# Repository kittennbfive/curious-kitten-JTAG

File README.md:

# curious-kitten-JTAG
  
*Hey kitten, find the JTAG-interface!*  

## What is this?
This is my version of the well-known [JTAGulator](http://www.grandideastudio.com/jtagulator/), made from scratch using different components and my own code. It is work in progress. I appreciate constructive feedback and testing, especially because i don't have a lot of targets to try my tool on.

## Licence and disclaimer
All code is licenced under AGPLv3+. The hardware (schematics, PCB-layout) is distributed under CC BY-SA 4.0. Everything is provided WITHOUT ANY WARRANTY! It is experimental stuff! Before using this tool for reverse-engineering please make sure it is legal to do so in your country. Also note that messing with unknown pins on a device can have nasty consequences, from crashes to fried silicon or even fatal explosions. As i said, **use at your own risk!**

## You need a JTAGulator? It's for sale, just buy one!
Well, the JTAGulator is certainly a really nice tool, but it is quite expensive (Parallax sells them for $189.00 as of today; Adafruit for $199.95). I wanted to make a more economic and simpler version and add some extra-features (with more or less success, read on...).

## Overview and features
The main part of this tool is an ATmega16A. It's available in DIP, has quite a few GPIOs and i had some in my parts bin. As many, many IC it is (sadly) currently unobtainium from the well-known distributors, but you can still get it on Aliexpress. The older ATmega16 without A should work fine too. Other main parts are 2 CD4067 (modules from Aliexpress) and 2 74HC595 (Aliexpress too).  

### Features/Specifications
* 24 channels
* can work with 3,3V or 5V as does your DUT (device under test) or - **NEW** - with optional levelshifters down to 1,2V (TXS0108E) (some commands/features will be unavailable in this mode)
* generic serial interface (115200 8N1), no special software or drivers needed on your PC
* automatic detection of IO-type (input or output, floating or with a pullup/down) to avoid driving outputs and to speed up the brute-force JTAG searching. This feature does not really work as intended for reasons i can't change. See below. *not available when using levelshifters*
* possibility to do some basic exploration of a found JTAG-interface (number of TAP in the chain, ...) (*)
* possibility to "wiggle" several other pins while searching for JTAG in case there is some "Reset", "JTAG-enable" or other signal that need to be driven high/low to make JTAG work. *not yet supported in levelshifter mode*
* pluggable current limiting resistors (THT parts or small extra PCB with SMD) for flexibility
* easy to make so mainly DIP, i only used SMD for a few passives because it's convenient (and 0805 is still quite easy to solder). You could redesign the entire board without any SMD-part. Using a few SMD-parts i managed to get the 2 layer PCB just under 10x10cm (-> cheap to manufacture).
* (much) cheaper than the JTAGulator. I did not do the maths but i would guess $30 or less as a ballpark figure.
* (planed) possibility to reset the DUT while searching for JTAG or doing other stuff (polarity of reset-signal configurable)
* (planed) possibility to power-cycle the DUT (MOSFET)
* (planed) monitoring of the current consumption of the DUT / overcurrent-protection
  
The planed features are currently not implemented but might be at some point. The PCB has spots for most of the needed components, except for the current-monitoring for which there are only testpads to connect an extra PCB. I did it this way because i was in a hurry to order the PCB and didn't had time to select an appropriate high-side current-sense IC (that would probably be unobtainium anyway...). Also selecting an "appropriate" IC to be put onto the main PCB directly is difficult (or even impossible) because there can be many different DUT, from portable stuff using microamps to big stuff using amps (or even AC or something).  

(*) Notice: This tool is not meant to be an universal JTAG-adapter, but rather a search tool. Once you identified the pins i suggest using a dedicated JTAG-adapter (i have a FT232H - beware it's 3,3V - that works great for this and other purposes) and some software like OpenOCD to read the IDENT-register (if it exists) and further mess with your DUT.

## Theory of operation
Having a copy of the schematic (`schematic.pdf`) and the code at hand while reading this part is recommanded.

### Overview/Basics
The ATmega16A is obviously the brain of the entire device. It receives commands via UART and uses a custom parser to dispatch to whatever function is wanted by the user. Each of the 24 channels is connected (via a current limiting resistor for safety) to a GPIO of the AVR. This allows the channel/pin to be an input (high-Z or with pullup) or an output. The two CD4067 are used to route the selected channel to an analog input of the internal ADC. They also allow to put a high-impedance signal (Vcc/2) on a channel for floating input detection. Because i needed a few more pins mainly to control the 4067 i added two 74HC595 with software-SPI on the AVR.
  
### IO-type identification
As said above the AVR will try to autodetect what is connected to each channel, ie
* an active (->low output impedance) digital output (or a direct connection to Vcc or GND, this is impossible to tell, just power everything off and use a multimeter in continuity mode to find Vcc/GND-pins and don't connect them to the AVR - although doing so should be safe because of the current limiting resistors)
* a floating input
* an input with a pullup to Vcc
* an input with a pulldown to GND
* some analog stuff or some variable signal that doesn't look digital (these pins will be ignored later).
#### Algorithm
The code i describe here is located in `pindir_ident.c`. It uses the following approach:
1. connect a high-impedance signal of Vcc/2 (voltage divider using 2 470k resistors) to the tested channel and measure the voltage using the internal ADC several times. If the values are fluctuating a lot the channel is probably not a digital IO -> ignore it. If the voltage is stable at around Vcc/2 we probably have a floating input. As you can see in the schematic both CD4067 have the Vcc/2-signal on a pin, so enabling *both* with the correct settings will connect Vcc/2 to the channel and also the channel to the analog input of the AVR.
2. configure the AVR-GPIO corresponding to the channel as an output, switch it to GND and then Vcc and measure the voltage once for each level. Because we could have an output of the DUT connected to the channel we need the protection resistors here to avoid blowing stuff up. If the measured voltage remains near Vcc or GND in both states we have either an active output (->low impedance) or a direct connection to Vcc/GND.
3. If the voltage drops to (almost) 0V with the AVR outputting a low-signal the channel is probably connected to an input with a pullup.
4. If the voltage goes up to (almost) Vcc while the AVR outputs a high-signal the channel is probably connected to an input with a pulldown.
#### Limitations
Obviously this approach is not perfect, for several reasons:
- Depending on the value used for the protection resistor the AVR might not be able to override a pullup/down completly, the voltage will be *somewhere between* Vcc and GND and the identification of the channel will fail. However using a too small protection resistor value could damage the DUT and/or the AVR.
- The value of pullups/pulldowns is variable between devices, it can be as low as let's say 1k or as high as let's say 470k. This makes automatic detection tricky.
- The state of a pin on the DUT can change, ie an output can be in high-Z mode when the AVR scans the channels. This is especially true for TDO on some (a lot? all?) devices if the JTAG state-machine is in reset or idle-mode where it usually will be. Optionally on some devices the TDO-pin has a pullup too.
- An output can toogle while the AVR scans the channels, in this case the AVR could report an analog pin to be ignored because the voltage changed a lot between measurements (step 1 above). *In doubt check with a scope.*  
  
All values used for this algorithm are configurable at compile-time (#define) and some tweaking might be needed. Sadly i don't have a lot of different devices with JTAG to test my code. I don't think there is enough space left in the AVR to make all these values *runtime*-configurable.

### Searching for JTAG
The code is in file `jtag.c`. I assume you are familiar with JTAG, if not please ask Wikipedia or a local expert or ...
#### The basic idea
Well, i did not invent anything. There are several documented tools like mine on the internet and some really useful papers and presentations available. The basic idea is always to try all possible combinations of pins/channels while sending some valid instructions/data. Precisely my tool tries to set all TAP (there might be several chained!) in BYPASS-mode (luckely this command is standardised), then clock in some known pattern on TDI and watch if it comes back on TDO.
#### Optimisations
To make things faster my code will monitor all possible outputs of the DUT *at the same time*. This can dramatically speed up things. Also the specification for JTAG recommands (or is it even mandatory?) pullups on TDI and TMS, so there is an option in the code to only consider inputs of the DUT that have these pullups as candidates for TDI and TMS.
#### Searching with pin-wiggling enabled
*not (yet) supported in levelshifter mode*  
As i said there might be (are they actually?) some DUT that needs some inputs to be pulled high/low to enable JTAG (i would appreciate an example of a device if you know one). The current code allows you to specify the number of pins to be wiggled simultaneously (because trying all combinations on like 20 pins would take *ages* and is probably rarely if ever needed). It will then try all possible combinations on the number of specified channels while looking for JTAG on the remaining channels. To speed things up the AVR will not set pins that already have a pullup/down to high/low but skip the concerned combinations.

## Exploring the (hopefully) discovered interface
Again, i did not invent anything.
### Get number of TAP in the chain
This works because the BYPASS-instruction is mandatory and standardised and the corresponding data register is always 1 bit wide. The code will set all TAP to BYPASS, clock in a lot of '1' to all the data registers and then clock in a single '0' and count how many clock cycles it takes for this '0' to get trough the chain. 
### Get the length of the instruction register
The basic idea is the same as above. Clock in a lot of '1' to the IR, then clock in a single '0' and wait for it to come back on TDO.
### Get the lengths of the data registers
Same as above except that that *data register* is probed and this for every single possible instruction. **Dangerous, see below!**

## The serial interface / commands
The serial interface runs at 115200 8N1 with the same voltage as the AVR (3,3V or 5V - be careful to select an appropriate USB-to-UART-thingie). Each command is terminated with enter. Currently backspace does not work (might be fixed at some point) and there is no way to scroll to already tipped commands like inside a Linux-terminal (won't be implemented). By default the AVR will send back/mirror entered characters, this can be configured at compile-time (inside `main.c`).
### reset
Well, this should be clear. Reset everything, configure all channels as inputs, ...
### allinp
Configure all channels as inputs without pullup but don't forget anything else that has been configured/discovered.
### devmode (normal|shift)
Switch between "normal" mode (full functionality but limited to 3,3V-5V) and levelshifter ("shift") mode. See below.
### channels $nb
Set the number of used channels, from 4 to 24. Don't make this number bigger than needed because the more channels are used the slower is the search for JTAG. This command is usually the first you need to use (in normal mode).
### ident (*not available in levelshifter mode*)
Do automated IO-type identification and print summary. This command is usually the second command you want to use.  
The following characters/abbreviations are used. The directions are seen from the view of the DUT.
- `--` Channel was not probed.
- `??` Identification failed.
- `a ` Channel might be an analog voltage or something that was fluctuating during the probing.
- `d ` Channel was disabled by user.
- `I ` Floating input.
- `PU` Input with pullup resistor.
- `PD` Input with pulldown resistor.
- `O ` Output.
### chstate
Print summary of set IO-types, useful if you get lost after manual adjustments (see below).
### setmode $channel $mode (*not available in levelshifter mode*)
Manually set the mode of a channel. Be aware that if you use `ident` again your changes will be lost.  
$channel is a number from 0 to 23.  
$mode can be one of "disabled", "input", "inputPU" (input with pullup), "inputPD" (input with pulldown), "output". The directions are seen from the DUT, ie "output" means the channel is an output on the DUT.
### override (inputs|unknown) (yes|no) (*not available in levelshifter mode*)
As i said above the automated IO-type detection is far from perfect. A (currently inactive) output of the DUT will be detected as input, so sometimes you won't see any outputs on the summary (command `chstate`). However JTAG always has one output, so there must be at least one channel configured as an output on the DUT to make the JTAG-search work. The command `override inputs yes` tells the code to also check channels that where detected as DUT-inputs for valid data (TDO). The command `override unknown yes` tells the code to also consider (ie *not* ignore) channels for which the IO-type couldn't been autodetected. *This is potentially dangerous for your DUT!* Remember the disclaimer above.
### tdopullup (yes|no) (*not available in levelshifter mode*)
Enable the internal pullup of the AVR before checking a channel for valid TDO-data. This is needed to detect the JTAG-interface of a "naked" ATmega16A. I don't really understand this as the datasheet states that TDO is left floating but only while the state machine is not shifting data (bug in my code??). You probably don't need this but it might be worth a try if everything else fails. Note that the protection resistor must not be a too high value because this will prevent the DUT from pulling the input of the AVR low! With something like 1k it's fine, with like 47k it is not. 
### jtag1 [ignore] [dontstop]
This is the actual search-command *without* pin-wiggling. It can take up to 2 optional arguments:
- `ignore` tells the code to not consider channels/pins that don't have the mandatory(?) pullup as possible candidates for TDI and TMS. Using this option can dramatically speed up the search but it might fail if there is no pullup on TDI and/or TMS or if the autodetection (`ident`) didn't work. *not available in levelshifter mode*
- `dontstop` tells the code *not* to stop after having found a valid JTAG interface. This is useful as a sanity check, normally there should be a single JTAG-interface. If the code reports a lot of them there is something wrong, in case of a naked ATmega16A it is the pullup on TDO that is missing (use `tdopullup yes`).
### jtag2 $number_of_pins_to_wiggle [ignore]
(*not yet available in levelshifter mode*)  
This is the command for searching while "wiggling" the specified number of pins (try `jtag1` first and then `jtag2 1`). Optionally you can specify `ignore` as for `jtag1`, see just above.
### setlevel $channel (0/1)
Set a channel that is configured / was detected as an output to low or high. This can be used for setting needed pins found by `jtag2`.
### taps
Get the number of TAP in the chain. Will only work if a JTAG-interface has been detected by the search-functions. If it reports 0 something is wrong, check everything and maybe try `jtag1 dontstop`, see above.
### irlen
Get the length of the instruction register. Will only work if `taps` detected a single tap.
### drlen
Get the lengths of the data registers for each instruction. Will only work if `taps` detected a single tap and `drlen` detected a valid length (!=0). **WARNING: This can REALLY mess up your DUT as it writes to every data register without knowing the effects! Use with great caution and - i say it again - at your own risk!**

## Optional levelshifter-support
To be able to probe some DUT that uses 1,8V i made this uh - contraption with 3 TXS0108E modules. It's somewhat messy but i didn't want to wait for an industrial PCB.
  
In this mode power the main board from 5V and type `devmode shift` as first command.  
A conceptual schematic of this module is in `levelshifter.pdf`. Adjust this depending on the hardware you have (IC or modules or other levelshifters). I don't have a PCB-layout or similar stuff.  
The TXS0108E is unobtainium from the well-known distributors (back in stock estimated in 2024! :( ), but you can get modules from places like Aliexpress. However 2 out of 3 modules i ordered have one broken channel ([insert nasty words here]), so i added some code to ignore defective channels (configurable at compile-time) while waiting for replacement IC. Look at `channels.c`.

## Statistics
```
$ cloc *.c *.h
      17 text files.
      17 unique files.                              
       0 files ignored.

github.com/AlDanial/cloc v 1.86  T=0.02 s (1106.0 files/s, 129537.0 lines/s)
-------------------------------------------------------------------------------
Language                     files          blank        comment           code
-------------------------------------------------------------------------------
C                                9            318             85           1325
C/C++ Header                     8             76             45            142
-------------------------------------------------------------------------------
SUM:                            17            394            130           1467
-------------------------------------------------------------------------------
```
The ATmega16A is already quite full, not too much space left... Compiled with -O2 as we want speed but with -O3 the firmware does not fit into the available 16kB.
```
$ avr-size avr.elf
   text	   data	    bss	    dec	    hex	filename
  13988	    432	    154	  14574	   38ee	avr.elf
```

## Example output
The file `log_jtag_atmega16a.txt` contains a complete example/log while searching for the (documented but let's suppose it isn't) JTAG-interface of an ATmega16A.  
The file `log_jtag_fpga.txt` contains the same thing for some FPGA-board.

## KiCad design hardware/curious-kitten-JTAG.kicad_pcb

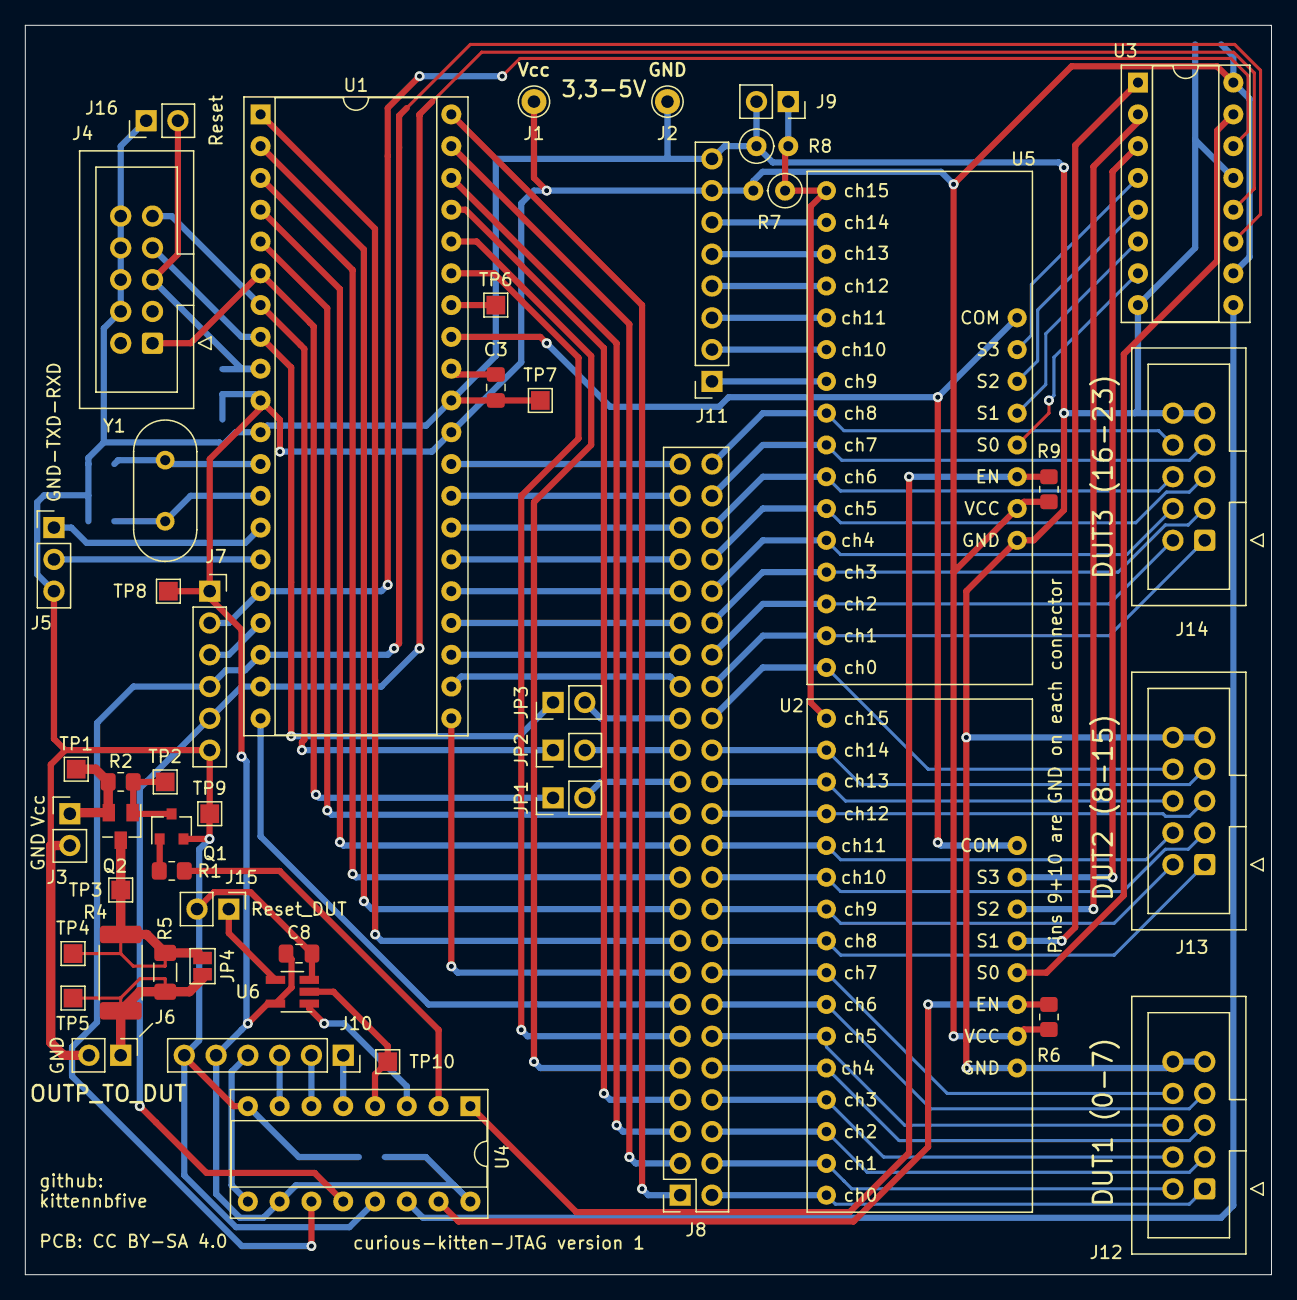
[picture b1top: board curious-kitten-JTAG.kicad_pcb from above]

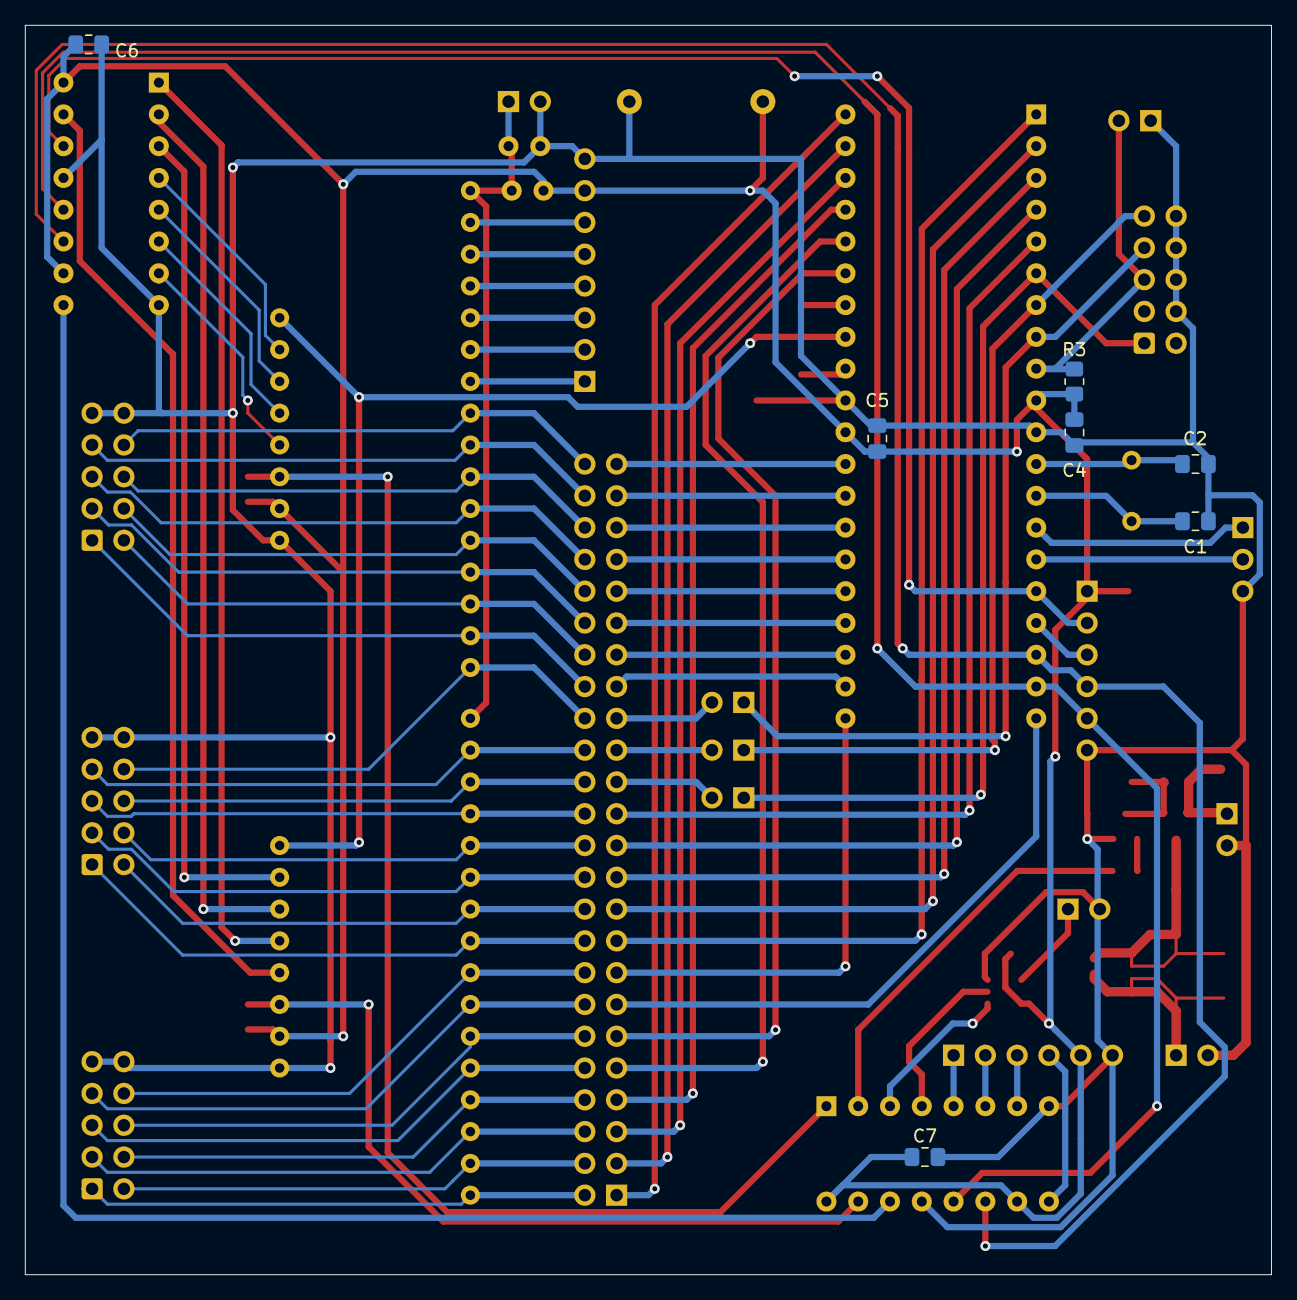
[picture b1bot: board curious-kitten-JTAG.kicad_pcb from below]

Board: 2 copper layers, 99.6 x 99.8 mm, 56 parts (7 on the bottom side), 96 nets.

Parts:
C1, C2: 22p; C_0805_2012Metric_Pad1.18x1.45mm_HandSolder
C3, C4, C5, C6, C7, C8: 100n; C_0805_2012Metric_Pad1.18x1.45mm_HandSolder
J1: Vcc; Pin_D1.0mm_L10.0mm
J2: GND; Pin_D1.0mm_L10.0mm
J3: Vcc_DUT_in; PinHeader_1x02_P2.54mm_Vertical
J4: prog; IDC-Header_2x05_P2.54mm_Vertical
J5: UART; PinHeader_1x03_P2.54mm_Vertical
J6: Vcc_DUT_out; PinHeader_1x02_P2.54mm_Vertical
J7: ext_SPI; PinSocket_1x06_P2.54mm_Vertical
J8: resistors; PinSocket_2x24_P2.54mm_Vertical
J9: half_Vcc; PinSocket_1x02_P2.54mm_Vertical
J10: ext_595_2; PinSocket_1x06_P2.54mm_Vertical
J11: ext_4067; PinSocket_1x08_P2.54mm_Vertical
J12: DUT_1; IDC-Header_2x05_P2.54mm_Vertical
J13: DUT_2; IDC-Header_2x05_P2.54mm_Vertical
J14: DUT_3; IDC-Header_2x05_P2.54mm_Vertical
J15: Reset_DUT_out; PinHeader_1x02_P2.54mm_Vertical
J16: Reset_AVR; PinHeader_1x02_P2.54mm_Vertical
JP1, JP2, JP3: Jumper_2_Bridged; PinHeader_1x02_P2.54mm_Vertical
JP4: SolderJumper_2_Open; SolderJumper-2_P1.3mm_Open_Pad1.0x1.5mm
Q1: BC847; SOT-23
Q2: FDN306P; SuperSOT-3
R1: 1k; R_0805_2012Metric_Pad1.20x1.40mm_HandSolder
R2, R3: 10k; R_0805_2012Metric_Pad1.20x1.40mm_HandSolder
R4: shunt1; R_2512_6332Metric_Pad1.40x3.35mm_HandSolder
R5: shunt2; R_1206_3216Metric_Pad1.30x1.75mm_HandSolder
R6, R9: 100k; R_0805_2012Metric_Pad1.20x1.40mm_HandSolder
R7, R8: 100k; R_Axial_DIN0207_L6.3mm_D2.5mm_P2.54mm_Vertical
TP1, TP2, TP3, TP4, TP5, TP6, TP7, TP8, TP9, TP10: TestPoint; TestPoint_Pad_1.5x1.5mm
U1: ATmega16A-PU; DIP-40_W15.24mm_Socket
U2, U5: CD4067_module
U3, U4: 74HC595; DIP-16_W7.62mm_Socket
U6: SN74LVC1G125DBVR; SOT-23-5_HandSoldering
Y1: 7,3728M; Crystal_HC49-U_Vertical

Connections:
/4067_1_A: U2.10, U3.15
/4067_1_B: U2.11, U3.1
/4067_1_C: U2.14, U3.2
/4067_1_D: U2.13, U3.3
/4067_1_EN: R6.1, U2.15, U4.15
/4067_2_A: U3.7, U5.10
/4067_2_B: U3.6, U5.11
/4067_2_C: U3.5, U5.14
/4067_2_D: U3.4, U5.13
/4067_2_EN: R9.1, U4.1, U5.15
/CLK: J7.4, U1.18, U3.11, U4.11
/MOSI: J7.2, U1.16, U3.14
/RST_DUT_en: U4.3, U6.1
/RST_DUT_sig: TP10.1, U4.4, U6.2
/RXD: J5.1, U1.14
/Reset: J4.5, J16.2, R3.1, U1.9
/TXD: J5.2, U1.15
/avr_ch0: J8.1, U1.40
/avr_ch1: J8.3, U1.39
/avr_ch2: J8.5, U1.38
/avr_ch3: J8.7, U1.37
/avr_ch4: J8.9, U1.36
/avr_ch5: J8.11, U1.35
/avr_ch6: J8.13, U1.20
/avr_ch7: J8.15, U1.21
/avr_ch8: J8.17, U1.1
/avr_ch9: J8.19, U1.2
/avr_ch10: J8.21, U1.3
/avr_ch11: J8.23, U1.4
/avr_ch12: J8.25, U1.5
/avr_ch13: J8.27, JP1.2
/avr_ch14: J8.29, JP2.2
/avr_ch15: J8.31, JP3.2
/avr_ch16: J8.33, U1.22
/avr_ch17: J8.35, U1.23
/avr_ch18: J8.37, U1.24
/avr_ch19: J8.39, U1.25
/avr_ch20: J8.41, U1.26
/avr_ch21: J8.43, U1.27
/avr_ch22: J8.45, U1.28
/avr_ch23: J8.47, U1.29
/ch0: J8.2, J12.1, U2.9
/ch1: J8.4, J12.2, U2.8
/ch2: J8.6, J12.3, U2.7
/ch3: J8.8, J12.4, U2.6
/ch4: J8.10, J12.5, U2.5
/ch5: J8.12, J12.6, U2.4
/ch6: J8.14, J12.7, U2.3
/ch7: J8.16, J12.8, U2.2
/ch8: J8.18, J13.1, U2.23
/ch9: J8.20, J13.2, U2.22
/ch10: J8.22, J13.3, U2.21
/ch11: J8.24, J13.4, U2.20
/ch12: J8.26, J13.5, U2.19
/ch13: J8.28, J13.6, U2.18
/ch14: J8.30, J13.7, U2.17
/ch15: J8.32, J13.8, U5.9
/ch16: J8.34, J14.1, U5.8
/ch17: J8.36, J14.2, U5.7
/ch18: J8.38, J14.3, U5.6
/ch19: J8.40, J14.4, U5.5
/ch20: J8.42, J14.5, U5.4
/ch21: J8.44, J14.6, U5.3
/ch22: J8.46, J14.7, U5.2
/ch23: J8.48, J14.8, U5.23
/half_Vcc: J9.1, R7.1, R8.2, U2.16, U5.16
/latch_595: J7.5, U1.19, U3.12, U4.12
/prog_MISO: J4.9, JP2.1, U1.7
/prog_MOSI: J4.1, JP1.1, U1.6
/prog_SCK: J4.7, JP3.1, U1.8
/sense_curr_DUT: TP6.1, U1.34
/sense_pin: U1.33, U2.1, U5.1
/switch_Vcc_DUT: R1.2, U4.2
GND: C1.2, C2.1, C3.1, C4.2, C5.2, C6.2, C7.2, C8.2, J2.1, J3.2, J4.4, J4.6, J4.8, J4.10, J5.3, J6.2, J7.6, J9.2, J10.6, J11.8, J12.9, J12.10, J13.9, J13.10, J14.9, J14.10, J15.2, J16.1, Q1.2, R8.1, TP7.1, TP9.1, U1.11, U1.31, U2.12, U3.8, U3.13, U4.8, U4.13, U5.12, U6.3
unnamed: C1.1, U1.13, Y1.1
unnamed: C2.2, U1.12, Y1.2
unnamed: C3.2, U1.32
unnamed: J3.1, Q2.2, R2.1, TP1.1
unnamed: J6.1, JP4.2, R4.1, R5.1, TP5.1
unnamed: J7.3, U1.17
unnamed: J10.1, U4.5
unnamed: J10.2, U4.6
unnamed: J10.3, U4.7
unnamed: J10.4, U4.9
unnamed: J11.1, U5.22
unnamed: J11.2, U5.21
unnamed: J11.3, U5.20
unnamed: J11.4, U5.19
unnamed: J11.5, U5.18
unnamed: J11.6, U5.17
unnamed: J15.1, U6.4
unnamed: JP4.1, Q2.3, R4.2, R5.2, TP3.1, TP4.1
unnamed: Q1.1, R1.1
unnamed: Q1.3, Q2.1, R2.2, TP2.1
unnamed: U3.9, U4.14
VCC: C4.1, C5.1, C6.1, C7.1, C8.1, J1.1, J7.1, J10.5, J11.7, R3.2, R6.2, R7.2, R9.2, TP8.1, U1.10, U1.30, U2.24, U3.10, U3.16, U4.10, U4.16, U5.24, U6.5

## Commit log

2022-09-02 typo

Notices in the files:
hardware/curious-kitten-JTAG.kicad_pcb:
PCB: CC BY-SA 4.0
